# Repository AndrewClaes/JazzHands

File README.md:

# JazzHands
Home of the Hybrid Saxophone

This project is based around the SparkFun ESP32 Thing.
Following the instructions below,
you can equip any saxophone with extended programmable MIDI-output.
It has a control input and a standard DIN MIDI output. 
The controller can be battery powered and supports charging on 5V USB.

The system makes use of unipolar hall effect switches, mounted near the corresponding moving parts on the body of the saxophone.
Magnets are attached to the corresponding moving parts on the keywork.

Please visit 
https://www.instructables.com/Jazz-Hands-Hybrid-Saxophone/

more info:
https://andrewclaes.net

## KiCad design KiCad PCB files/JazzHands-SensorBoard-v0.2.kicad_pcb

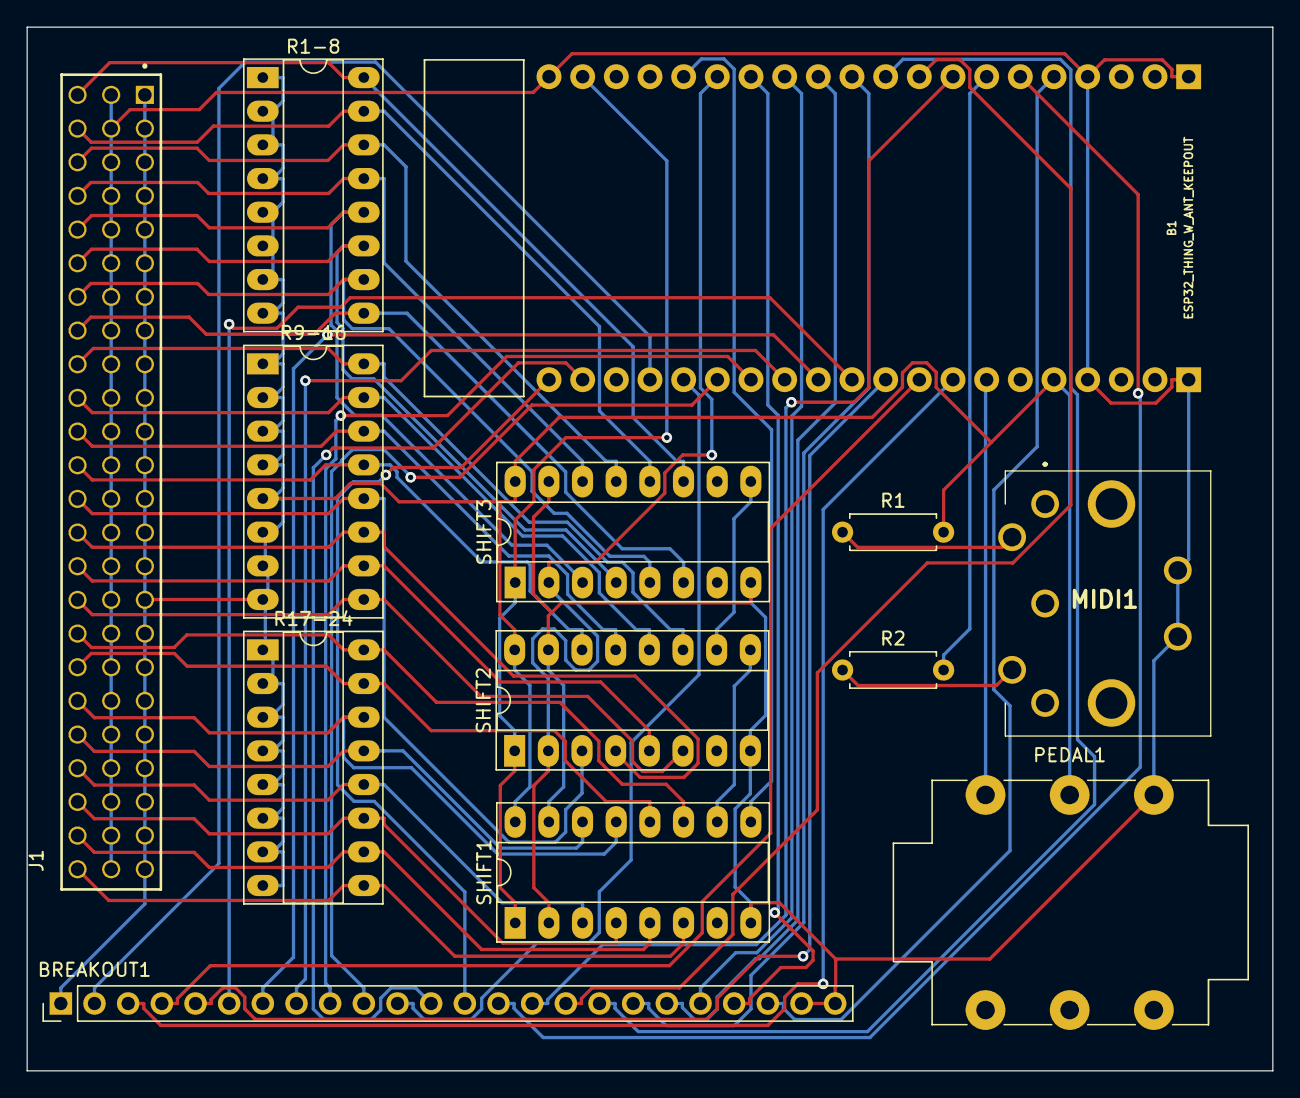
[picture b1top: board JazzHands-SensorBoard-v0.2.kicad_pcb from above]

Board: 2 copper layers, 94.0 x 78.7 mm, 13 parts (0 on the bottom side), 56 nets.

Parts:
B1: ESP32_THING_W_ANT_KEEPOUT; ESP32_THING
BREAKOUT1: extra; PinHeader_1x24_P2.54mm_Vertical
J1: SSQ-124-01-T-T; SAMTEC_SSQ-124-01-T-T
MIDI1: 57PC5F
PEDAL1: AudioJack; Jack_6.35mm_Neutrik_NMJ6HCD2_Horizontal
R1, R2: 200; R_Axial_DIN0207_L6.3mm_D2.5mm_P7.62mm_Horizontal
R1-8, R9-16, R17-24: 100k; DIP-16_W7.62mm_Socket_LongPads
SHIFT1, SHIFT2, SHIFT3: 74HC165; DIP-16_W7.62mm_Socket_LongPads

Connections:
Earth: B1.1 (GND), B1.4 (GND), B1.21 (GND), B1.37 (GND), B1.40 (GND), BREAKOUT1.23, BREAKOUT1.24, J1.02, J1.05, J1.08, J1.11, J1.14, J1.17, J1.20, J1.23, J1.26, J1.29, J1.32, J1.35, J1.38, J1.41, J1.44, J1.47, J1.50, J1.53, J1.56, J1.59, J1.62, J1.65, J1.68, J1.71, MIDI1.6 (GND_1), MIDI1.7 (GND_2), PEDAL1.S, SHIFT1.8, SHIFT1.15, SHIFT2.8, SHIFT2.15, SHIFT3.8, SHIFT3.15
unnamed: B1.5 (3V3), BREAKOUT1.1, J1.01, J1.04, J1.07, J1.10, J1.13, J1.16, J1.19, J1.22, J1.25, J1.28, J1.31, J1.34, J1.37, J1.40, J1.43, J1.46, J1.49, J1.52, J1.55, J1.58, J1.61, J1.64, J1.67, J1.70, PEDAL1.R, R1.2, R1-8.1, R1-8.2, R1-8.3, R1-8.4, R1-8.5, R1-8.6, R1-8.7, R1-8.8, R9-16.1, R9-16.2, R9-16.3, R9-16.4, R9-16.5, R9-16.6, R9-16.7, R9-16.8, R17-24.1, R17-24.2, R17-24.3, R17-24.4, R17-24.5, R17-24.6, R17-24.7, R17-24.8, SHIFT1.16, SHIFT2.16, SHIFT3.16
unnamed: B1.8 (12), BREAKOUT1.3
unnamed: B1.9 (14), BREAKOUT1.4
unnamed: B1.10 (27), BREAKOUT1.5
unnamed: B1.11 (26), BREAKOUT1.6
unnamed: B1.12 (25), BREAKOUT1.7
unnamed: B1.13 (35), BREAKOUT1.8
unnamed: B1.14 (34), BREAKOUT1.9
unnamed: B1.15 (33), BREAKOUT1.10
unnamed: B1.16 (32), BREAKOUT1.11
unnamed: B1.17 (39), BREAKOUT1.2
unnamed: B1.19 (37), BREAKOUT1.12
unnamed: B1.20 (36), BREAKOUT1.13
unnamed: B1.22 (21), SHIFT1.1, SHIFT2.1, SHIFT3.1
unnamed: B1.25 (22), SHIFT1.9
unnamed: B1.26 (19), SHIFT1.2, SHIFT2.2, SHIFT3.2
unnamed: B1.27 (23), BREAKOUT1.21
unnamed: B1.28 (18), BREAKOUT1.20
unnamed: B1.29 (5), BREAKOUT1.19
unnamed: B1.30 (15), BREAKOUT1.18
unnamed: B1.31 (2), BREAKOUT1.17
unnamed: B1.32 (0), BREAKOUT1.16
unnamed: B1.33 (4), BREAKOUT1.15
unnamed: B1.34 (17), R2.2
unnamed: B1.35 (16), BREAKOUT1.14
unnamed: B1.36 (3V3), BREAKOUT1.22
unnamed: J1.03, R1-8.16, SHIFT3.11
unnamed: J1.06, R1-8.15, SHIFT3.12
unnamed: J1.09, R1-8.14, SHIFT3.13
unnamed: J1.12, R1-8.13, SHIFT3.14
unnamed: J1.15, R1-8.12, SHIFT3.3
unnamed: J1.18, R1-8.11, SHIFT3.4
unnamed: J1.21, R1-8.10, SHIFT3.5
unnamed: J1.24, R1-8.9, SHIFT3.6
unnamed: J1.27, R9-16.16, SHIFT2.11
unnamed: J1.30, R9-16.15, SHIFT2.12
unnamed: J1.33, R9-16.14, SHIFT2.13
unnamed: J1.36, R9-16.13, SHIFT2.14
unnamed: J1.39, R9-16.12, SHIFT2.3
unnamed: J1.42, R9-16.11, SHIFT2.4
unnamed: J1.45, R9-16.10, SHIFT2.5
unnamed: J1.48, R9-16.9, SHIFT2.6
unnamed: J1.51, R17-24.16, SHIFT1.11
unnamed: J1.54, R17-24.15, SHIFT1.12
unnamed: J1.57, R17-24.14, SHIFT1.13
unnamed: J1.60, R17-24.13, SHIFT1.14
unnamed: J1.63, R17-24.12, SHIFT1.3
unnamed: J1.66, R17-24.11, SHIFT1.4
unnamed: J1.69, R17-24.10, SHIFT1.5
unnamed: J1.72, R17-24.9, SHIFT1.6
unnamed: MIDI1.4, R1.1
unnamed: MIDI1.5, R2.1
unnamed: B1.7 (13), PEDAL1.T
unnamed: SHIFT1.10, SHIFT2.9
unnamed: SHIFT2.10, SHIFT3.9
